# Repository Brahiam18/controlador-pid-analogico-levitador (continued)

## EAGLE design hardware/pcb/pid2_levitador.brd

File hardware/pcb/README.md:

# Placa de 2 controladores PID analógicos con etapa de potencia

Placa de **una sola cara** para fabricar en baquela (transferencia de tóner o fotosensible) con **dos controladores PID independientes**. Para el levitador de cuatro bobinas se hacen **dos tarjetas iguales** (un solo plano, impreso dos veces). Cada controlador es idéntico al circuito del informe (2 × TL074CN por PID) y **trae su propia etapa de potencia** (convertidor tensión‑corriente con TIP122, banco de sensado de 3 × 1 Ω, protección y bornes para la bobina). Los dos PID de una tarjeta comparten los rieles de ±16 V, +5 V y GND; cada uno tiene su entrada de sensor (`VSEN`), su salida de control (`VPID`), su alimentación de bobina (`VBOB`/`PGND`) y su conexión de bobina.

| Dato | Valor |
|---|---|
| Tamaño de la placa | **170.2 × 116.8 mm** (17 × 11.7 cm): cabe en una baquela de 20 × 20 cm y el PDF se imprime 1:1 en una hoja A4 o Carta |
| Capas | 1 (cobre inferior) + puentes de alambre en el lado de componentes |
| Pistas de señal / pads / taladro | 0.7 mm / 2.0 mm / 0.9 mm (los pads de potencia usan 1.0 a 1.3 mm) |
| Pistas de potencia | 2.0 mm (`ISENSE`, `COILN`, `+VBOB`, `PGND`); unos 3.9 A con +10 °C de calentamiento, conviene **cubrirlas con estaño** |
| Separación mínima entre redes | 0.45 mm (medida sobre la geometría final) |
| Puentes de alambre | 24 en total, ninguno en redes de potencia; ver [`puentes.md`](puentes.md) |

## Archivos

| Archivo | Para qué sirve |
|---|---|
| [`pid2_levitador.sch`](pid2_levitador.sch) y [`pid2_levitador.brd`](pid2_levitador.brd) | Esquemático (una hoja por PID) y placa en formato EAGLE; Fusion los abre en Electronics |
| [`cobre_espejado_1a1.pdf`](cobre_espejado_1a1.pdf) | **Hoja de cobre espejado a escala 1:1** para imprimir y quemar la placa (imprimirla dos veces: una por tarjeta) |
| [`ensamble_1a1.pdf`](ensamble_1a1.pdf) | **Hoja del lado de componentes** (3 páginas: la placa completa 1:1 y cada PID ampliado): nombre de cada pieza y de cada pin de las regletas, borneras, TIP122 y diodos, amplificadores U1 a U8 marcados sobre cada TL074 y puentes en rojo (J1 a J24) |
| [`puentes.md`](puentes.md) | Lista de los 24 puentes con red, longitud y extremos |
| [`generador/`](generador/) | Código en Python que genera todo lo anterior a partir de un módulo ruteado (`modulo_ruteado.json`) |

## Cómo usarlos

**Abrir en Fusion.** En Fusion, usar "Cargar" y elegir `pid2_levitador.sch` y `pid2_levitador.brd` juntos; con la casilla "Crear diseño de la electrónica" marcada se obtiene un solo diseño de Electronics. Las piezas están en una biblioteca propia llamada `pid4`.

**Imprimir y quemar.** Imprimir `cobre_espejado_1a1.pdf` **sin escalar** ("tamaño real", sin "ajustar a página"); la hoja mide 210 × 279 mm y entra en A4 y en Carta. La regla de 50 mm al pie de la placa sirve para comprobar la escala. La hoja ya está espejada: el tóner va contra el cobre. El punto blanco en el centro de cada pad marca dónde taladrar. Taladros: 0.9 mm en general, 1.0 mm para el TIP122, 1.1 mm para el banco de sensado y 1.3 mm para el 1N5408 y las borneras.

**Soldar.** Imprimir también `ensamble_1a1.pdf`: sirve de guía para ubicar cada pieza. Primero los puentes de alambre aislado en el lado de componentes (ver [`puentes.md`](puentes.md)), después resistencias, zócalos y diodos, y al final potenciómetros, capacitores, borneras y el TIP122. Cubrir con estaño las pistas anchas de potencia.

**Dos tarjetas.** Las dos placas son iguales. Para alimentarlas se unen por cable `+16V`, `-16V`, `GND` y `+5V` entre las regletas `J_PWR` de las dos tarjetas. El puente `JP_GND` (une la tierra de potencia con la de señal) se suelda en **una sola** de las cuatro etapas.

## Conexiones de cada PID

| Regleta | Pines | Función |
|---|---|---|
| `J_PWR` | 1 · 2 · 3 · 4 | `+16V` · `-16V` · `GND` · `+5V` (compartidos en la tarjeta: basta alimentar una sola regleta) |
| `J_IN` | 1 | `VSEN`, señal del sensor de posición |
| `J_OUT` | 1 | `VPID`, salida del controlador (1 V a 3 V); es solo punto de medida, la etapa de potencia ya lo toma internamente |
| `J_VBOB` (bornera) | `+VBOB` · `PGND` | Fuente de las bobinas: positivo y negativo. **Una fuente por PID** (o todos los pares en paralelo a la misma fuente) |
| `J_COIL` (bornera) | `BOB+` · `BOB-` | Bobina: `BOB+` va a `+VBOB` por la pista; `BOB-` va al colector del TIP122 |
| `JP_GND` | `GND` · `PGND` | Dos pads **sin pista entre ellos**: se unen con un alambre para juntar la tierra de potencia con la de señal (ver más abajo) |

`+5V` solo alimenta el divisor de `V_ref` (`R13`).

## Etapa de potencia (una por PID)

Es el circuito que armaste y simulaste en Proteus: un amplificador (U8) compara el voltaje de entrada con el voltaje sobre la resistencia de sensado y maneja la base de un TIP122, de modo que **la corriente de la bobina es proporcional a la salida del PID**. La bobina va entre `+VBOB` y el colector; el diodo 1N5408 en paralelo con la bobina absorbe el pico inductivo.

```mermaid
flowchart LR
    VPID["VPID (1 a 3 V)"] --> R17["R17 10 kΩ"] --> POT4["POT4 10 kΩ<br/>(calibración)"]
    POT4 -- cursor --> R16["R16 270 Ω"] --> U8["U8 (TL074, IC2 canal 4)<br/>entrada +"]
    U8 -- salida --> RB["RBASE 270 Ω"] --> D2["D2 1N4148<br/>(serie)"] --> Q1["Q1 TIP122"]
    Q1 -- emisor --> RS["RS: 3 × 1 Ω 5 W<br/>en paralelo = 0.33 Ω"] --> PG["PGND"]
    Q1 -- emisor / ISENSE --> R18["R18 1 kΩ"] --> U8m["U8 entrada −"]
    VB["+VBOB"] --> BOB["Bobina"] --> Q1
    D1["D1 1N5408"] -. "en paralelo con la bobina" .- BOB
```

Qué se agregó respecto a tu esquemático de Proteus, y por qué:

| Pieza | Para qué |
|---|---|
| **R17 + POT4** (divisor de calibración) | Con 3 resistencias de 1 Ω en paralelo el sensado vale **0.33 Ω**, no 1 Ω, así que la ganancia sube tres veces (`I = V/0.33 Ω`) y 3 V a la entrada pedirían 9 A. El divisor devuelve la ganancia a un valor seguro y deja ajustar la corriente sin tocar el banco de potencia |
| **D2** (1N4148 en serie con la base) | Si el amplificador satura hacia −13 V, no empuja ese voltaje inverso a la unión base‑emisor del TIP122 (máx. 5 V inverso) |
| **R18** (1 kΩ) y **C3** (10 nF, opcional) | Solo si el lazo de corriente oscila con el TL074 (más rápido que el LM741 de la simulación): soldar `C3` entre la salida de U8 y su entrada −. Sin `C3`, `R18` no tiene efecto |
| **JP_GND** | Une `PGND` con `GND` en un solo punto |

### Por qué 3 resistencias y no 10

Cada resistencia de 1 Ω conduce `I/n` y disipa `(I/n)²` vatios, y el sensado total vale `1/n` Ω. A 4.5 A (el máximo del TIP122 con margen), con `n = 3` cada una disipa 2.25 W: menos de la mitad de sus 5 W. Con `n = 10` cada una solo disiparía 0.2 W, y el banco ocupaba casi la mitad de cada módulo.

| Resistencias por PID (`n`) | `R_S` | `R17` | Cada una a 3 A | Cada una a 4.5 A |
|:-:|:-:|:-:|:-:|:-:|
| 2 (no recomendado) | 0.5 Ω | 3.3 kΩ | 2.25 W | 5 W (en el límite) |
| **3 (la huella de la placa)** | **0.33 Ω** | **10 kΩ** | **1 W** | **2.25 W** |

La huella tiene 3 posiciones. Con 2 resistencias hay que cambiar `R17` a 3.3 kΩ y no queda margen para 4.5 A; con 1 sola no sirve.

### Ganancia y calibración

`I_bobina = V_cal / R_S` con `V_cal = k · V_PID` y `R_S = 0.33 Ω` (3 resistencias), es decir:

**`I_bobina ≈ 3 · k · V_PID`** con `k = R_b / (R17 + 10 kΩ)`, donde `R_b` es la resistencia del cursor de POT4 a masa (0 a 10 kΩ). Con `R17 = 10 kΩ`, `k` va de 0 a 0.5.

| Ajuste de POT4 | `k` | Ganancia | Corriente con `V_PID` = 2 V | Con `V_PID` = 3 V |
|---|:-:|:-:|:-:|:-:|
| Mínimo (cursor a masa) | 0 | 0 | 0 A | 0 A |
| Cursor al 67 % (`R_b` = 6.7 kΩ) | 0.33 | 1 A/V (como en tu simulación) | 2.0 A | 3.0 A |
| Máximo | 0.5 | 1.5 A/V | 3.0 A | 4.5 A |

El máximo (4.5 A) queda por debajo del límite del TIP122 (5 A continuos).

**Cómo calibrar.** (1) Con POT4 al mínimo, conectar la bobina y la fuente de `VBOB` (empezar con la fuente baja). (2) Con el objeto en su posición de equilibrio, subir POT4 hasta la corriente que necesites. (3) La corriente se mide como voltaje entre `ISENSE` (emisor del TIP122) y `PGND`: **0.33 V por cada amperio**.

### Disipación y fuente

El TIP122 trabaja en modo lineal: disipa `P = (V_BOB − I·(R_bobina + 0.33 Ω)) · I`. Como la resistencia de la bobina irá cambiando, conviene consultar esta tabla (se asume `Vce` mínimo de 2 V; "no llega" significa que la fuente no alcanza para esa corriente):

| Resistencia de la bobina | 12 V: 1 A | 12 V: 2 A | 12 V: 3 A | 20 V: 1 A | 20 V: 2 A | 20 V: 3 A |
|:-:|:-:|:-:|:-:|:-:|:-:|:-:|
| 2 Ω | 10 W | 15 W | 15 W | 18 W | **31 W** | **39 W** |
| 4 Ω | 8 W | 7 W | no llega | 16 W | 23 W | 21 W |
| 6 Ω | 6 W | no llega | no llega | 14 W | 15 W | no llega |
| 8 Ω | 4 W | no llega | no llega | 12 W | 7 W | no llega |

- Con bobinas de poca resistencia y 20 V, el TIP122 disipa decenas de vatios: **disipador grande (y ventilador)** o bajar la tensión de `VBOB`.
- La aleta del TIP122 es el colector (`BOB-`): si varios transistores comparten disipador, **aislarlos** con mica o silicona.
- Una fuente de 20 V / 6 A reparte 6 A entre las cuatro etapas (1.5 A por bobina si trabajan a la vez).
- Poner un **fusible de 5 A** en cada línea de `+VBOB` (fuera de la placa) mientras se afina.
- Los offsets del TL074 (unos mV) equivalen a decenas de mA con 0.33 Ω; el lazo de posición lo compensa, pero la corriente "cero" no será exacta.
- La caída en las pistas de potencia se suma al sensado; por eso el banco y `JP_GND` están cerca.

## Reparto de las etapas en los TL074CN

El TL074CN trae 4 amplificadores en un solo DIP‑14, así que las 7 etapas del informe (U1 a U7) más el convertidor tensión‑corriente de potencia (**U8**) caben en 2 integrados por controlador. Cada integrado se llama `IC1` o `IC2` en la placa (con el prefijo del PID, por ejemplo `P1_IC1`) y en la hoja de ensamble cada canal lleva escrita su etapa (cuadro amarillo).

| Etapa | Integrado | Canal | Salida (pin) | Entrada − (pin) | Entrada + (pin) |
|---|:-:|:-:|:-:|:-:|:-:|
| U6 · buffer de `V_ref` | IC1 | 1 | 1 | 2 | 3 |
| U1 · diferenciador de error | IC1 | 2 | 7 | 6 | 5 |
| U2 · proporcional | IC1 | 3 | 8 | 9 | 10 |
| U3 · integral | IC1 | 4 | 14 | 13 | 12 |
| U4 · derivativo | IC2 | 1 | 1 | 2 | 3 |
| U5 · sumador | IC2 | 2 | 7 | 6 | 5 |
| U7 · buffer de `V_off` | IC2 | 3 | 8 | 9 | 10 |
| **U8 · convertidor V‑I de potencia** | IC2 | 4 | 14 | 13 | 12 |

Alimentación de cada TL074CN: `+16V` en el pin 4 y `-16V` en el pin 11. Los valores de resistencias y capacitores de las etapas U1 a U7 son los del informe.

## Componentes (por PID, por tarjeta y para los 4 PID)

| Componente | Por PID | Por tarjeta (2 PID) | Para 4 PID (2 tarjetas) | Notas |
|---|:-:|:-:|:-:|---|
| TL074CN (DIP14) | 2 | 4 | 8 | Usar zócalos DIP14. Pin 1 arriba a la izquierda en todos los CI |
| TIP122 (TO‑220) | 1 | 2 | 4 | Con disipador; el pad cuadrado es la base (B), el del centro el colector (C) y el otro el emisor (E) |
| 1N5408 | 1 | 2 | 4 | `D1`, protección de la bobina. La raya marca el cátodo (pad hacia `+VBOB`) |
| 1N4148 | 1 | 2 | 4 | `D2`, en serie con la base. La raya marca el cátodo (pad hacia la base) |
| 1 Ω / 5 W axial | 3 | 6 | 12 | Banco `RS`; ver arriba por qué 3 |
| 10 kΩ | 10 | 20 | 40 | R1, R2, R3, R4, R5, R7, R8, R9, R_offset y R17 |
| 1 kΩ | 3 | 6 | 12 | R6, R10 y R18 |
| 270 Ω | 2 | 4 | 8 | R16 y RBASE |
| 1 MΩ | 1 | 2 | 4 | R11 |
| 160 kΩ | 2 | 4 | 8 | R12, R15 |
| 240 kΩ | 1 | 2 | 4 | R13 |
| 96 kΩ | 1 | 2 | 4 | R14 (valor calculado; no es de serie, ver más abajo) |
| 4.4 kΩ | 1 | 2 | 4 | R_bias (valor de tu montaje; no es de serie, ver más abajo) |
| Potenciómetro 22 kΩ | 2 | 4 | 8 | Pot1 (Kp) y Pot3 (Kd) |
| Potenciómetro 220 kΩ | 1 | 2 | 4 | Pot2 (Ki) |
| Potenciómetro 10 kΩ | 1 | 2 | 4 | Pot4 (corriente de la bobina) |
| Capacitor 1 µF | 2 | 4 | 8 | C1 (integrador) y C2 (derivador) |
| Capacitor 10 nF | 0 (opcional 1) | 0 (opcional 2) | 0 (opcional 4) | C3, solo si el lazo de corriente oscila |
| Borneras de tornillo de 2 vías, paso 5.08 | 2 | 4 | 8 | `J_VBOB` y `J_COIL` (corriente de varios amperios) |
| Regletas de pines | 8 pines | 16 pines | 32 pines | 1 × 4 (`J_PWR`), 2 × 1 (`J_IN`, `J_OUT`) y 1 × 2 (`JP_GND`) |

Resistencias axiales de 1/4 W a 7.62 mm, capacitores a 5.08 mm y potenciómetros de 3 pines a 5.08 mm (pin 1 = extremo, pin 2 = cursor, pin 3 = otro extremo). Las resistencias de 5 W miden unos 22 × 9.5 mm y se montan acostadas con 25.4 mm entre pads, en una fila de tres.

## Cosas a tener en cuenta

- **Capacitores sin polaridad.** `C1` y `C2` trabajan con señales de ambos signos, por lo que conviene usar poliéster (MKT) o cerámicos de 1 µF. Con un electrolítico, la polaridad queda invertida en una parte del ciclo.
- **`R_bias` y `R14` no son valores comerciales.** Para `R_bias` sirven 4.7 kΩ o 4.3 kΩ (la corriente de polarización es muy pequeña). Para `R14`, tomar 100 kΩ o 91 kΩ más 4.7 kΩ en serie y ajustar mirando `V_off`: en la protoboard se midieron −10.21 V frente a −10.1 V calculados. El informe sigue con `R14` como "falta medir" y con la errata 5 de `R_bias` sin resolver.
- **TL074CN en lugar de LM741.** La placa está hecha para el TL074CN. El informe, la lista de materiales general y las mediciones de la Tabla I todavía nombran al LM741; con TL074CN (entradas JFET, salida de unos ±13 V con ±16 V) los offsets y los valores prácticos pueden cambiar un poco.
- **Diferenciador (U1).** La placa sigue el esquemático de Proteus y las mediciones del montaje: `R1` recibe `V_ref` (entrada inversora) y `R3` recibe `V_sensor` (entrada no inversora), así que `V_e = V_sensor − V_ref`. La tabla de nomenclatura del informe dice lo contrario para `R1` y `R3`; conviene corregirla.
- **`V_ref` fijo.** `R12`/`R13` dan 2 V de referencia. Con un sensor Hall lineal (por ejemplo SS495A) el voltaje en el punto de equilibrio será cercano a 2.5 V más el aporte del imán, así que probablemente haga falta ajustar `V_ref` (por ejemplo con un trimmer en lugar de `R12`).
- **Puentes.** Son 24 en total (ninguno en redes de potencia); los más largos miden hasta unos 71 mm de alambre y varios pasan sobre otros componentes, por eso deben ser de alambre aislado. En el archivo EAGLE los puentes están dibujados en la capa Top.
- **Sin decoupling.** El diseño del informe no incluye capacitores de desacople; si hay ruido, se pueden soldar 100 nF entre cada alimentación del TL074CN (pines 4 y 11) y masa por el lado de soldadura.
- **Polaridad del control.** Si al subir `V_PID` la bobina atrae más o menos depende del sensor y del montaje; esta placa solo entrega corriente proporcional a `V_PID`.

## Qué se verificó y qué no

Verificado con scripts incluidos en [`generador/`](generador/) (`verify.py` y `xmlcheck.py`):
- Las 62 redes de la placa están completas (ningún pad queda sin conectar a su red) y no hay cortos entre redes.
- La separación mínima entre cobre de redes distintas es de 0.45 mm, también entre las pistas anchas de 2.0 mm.
- Los puentes no tocan pads ajenos ni se cruzan entre sí, y ninguna red de potencia usa puentes.
- El esquemático y la placa tienen las mismas piezas y las mismas conexiones.

**No** verificado: la placa no se ha fabricado ni probado, y el comportamiento de la etapa de potencia con el TL074CN (estabilidad del lazo de corriente, calentamiento) no se simuló: sale de tu esquemático de Proteus y de cálculos a mano. Las versiones anteriores de la placa se importaron en Fusion sin errores; esta versión usa el mismo exportador pero con símbolos nuevos (transistor, diodos, banco de sensado) y aún no se ha reabierto en Fusion. Los archivos `.sch` y `.brd` se escribieron a mano en el formato XML de EAGLE; si Fusion muestra algún aviso al importarlos, conviene revisarlo antes de quemar. Se recomienda probar un solo PID (con la bobina real a baja tensión y un fusible) antes de armar el resto.

## Regenerar

```bash
cd generador
pip install numpy matplotlib shapely
python3 build.py modulo_ruteado.json salida
```

Genera en `salida/` los archivos `.sch`, `.brd`, los dos PDF y la lista de puentes. Para buscar otra colocación y ruteo del módulo (otro tamaño o semilla): `python3 buscar_modulo.py 30 42 1,2,3 prueba` y luego `python3 a_json.py best_prueba.pkl modulo_ruteado.json`. El número de PID por tarjeta está en `assemble.py` (`NMOD`).

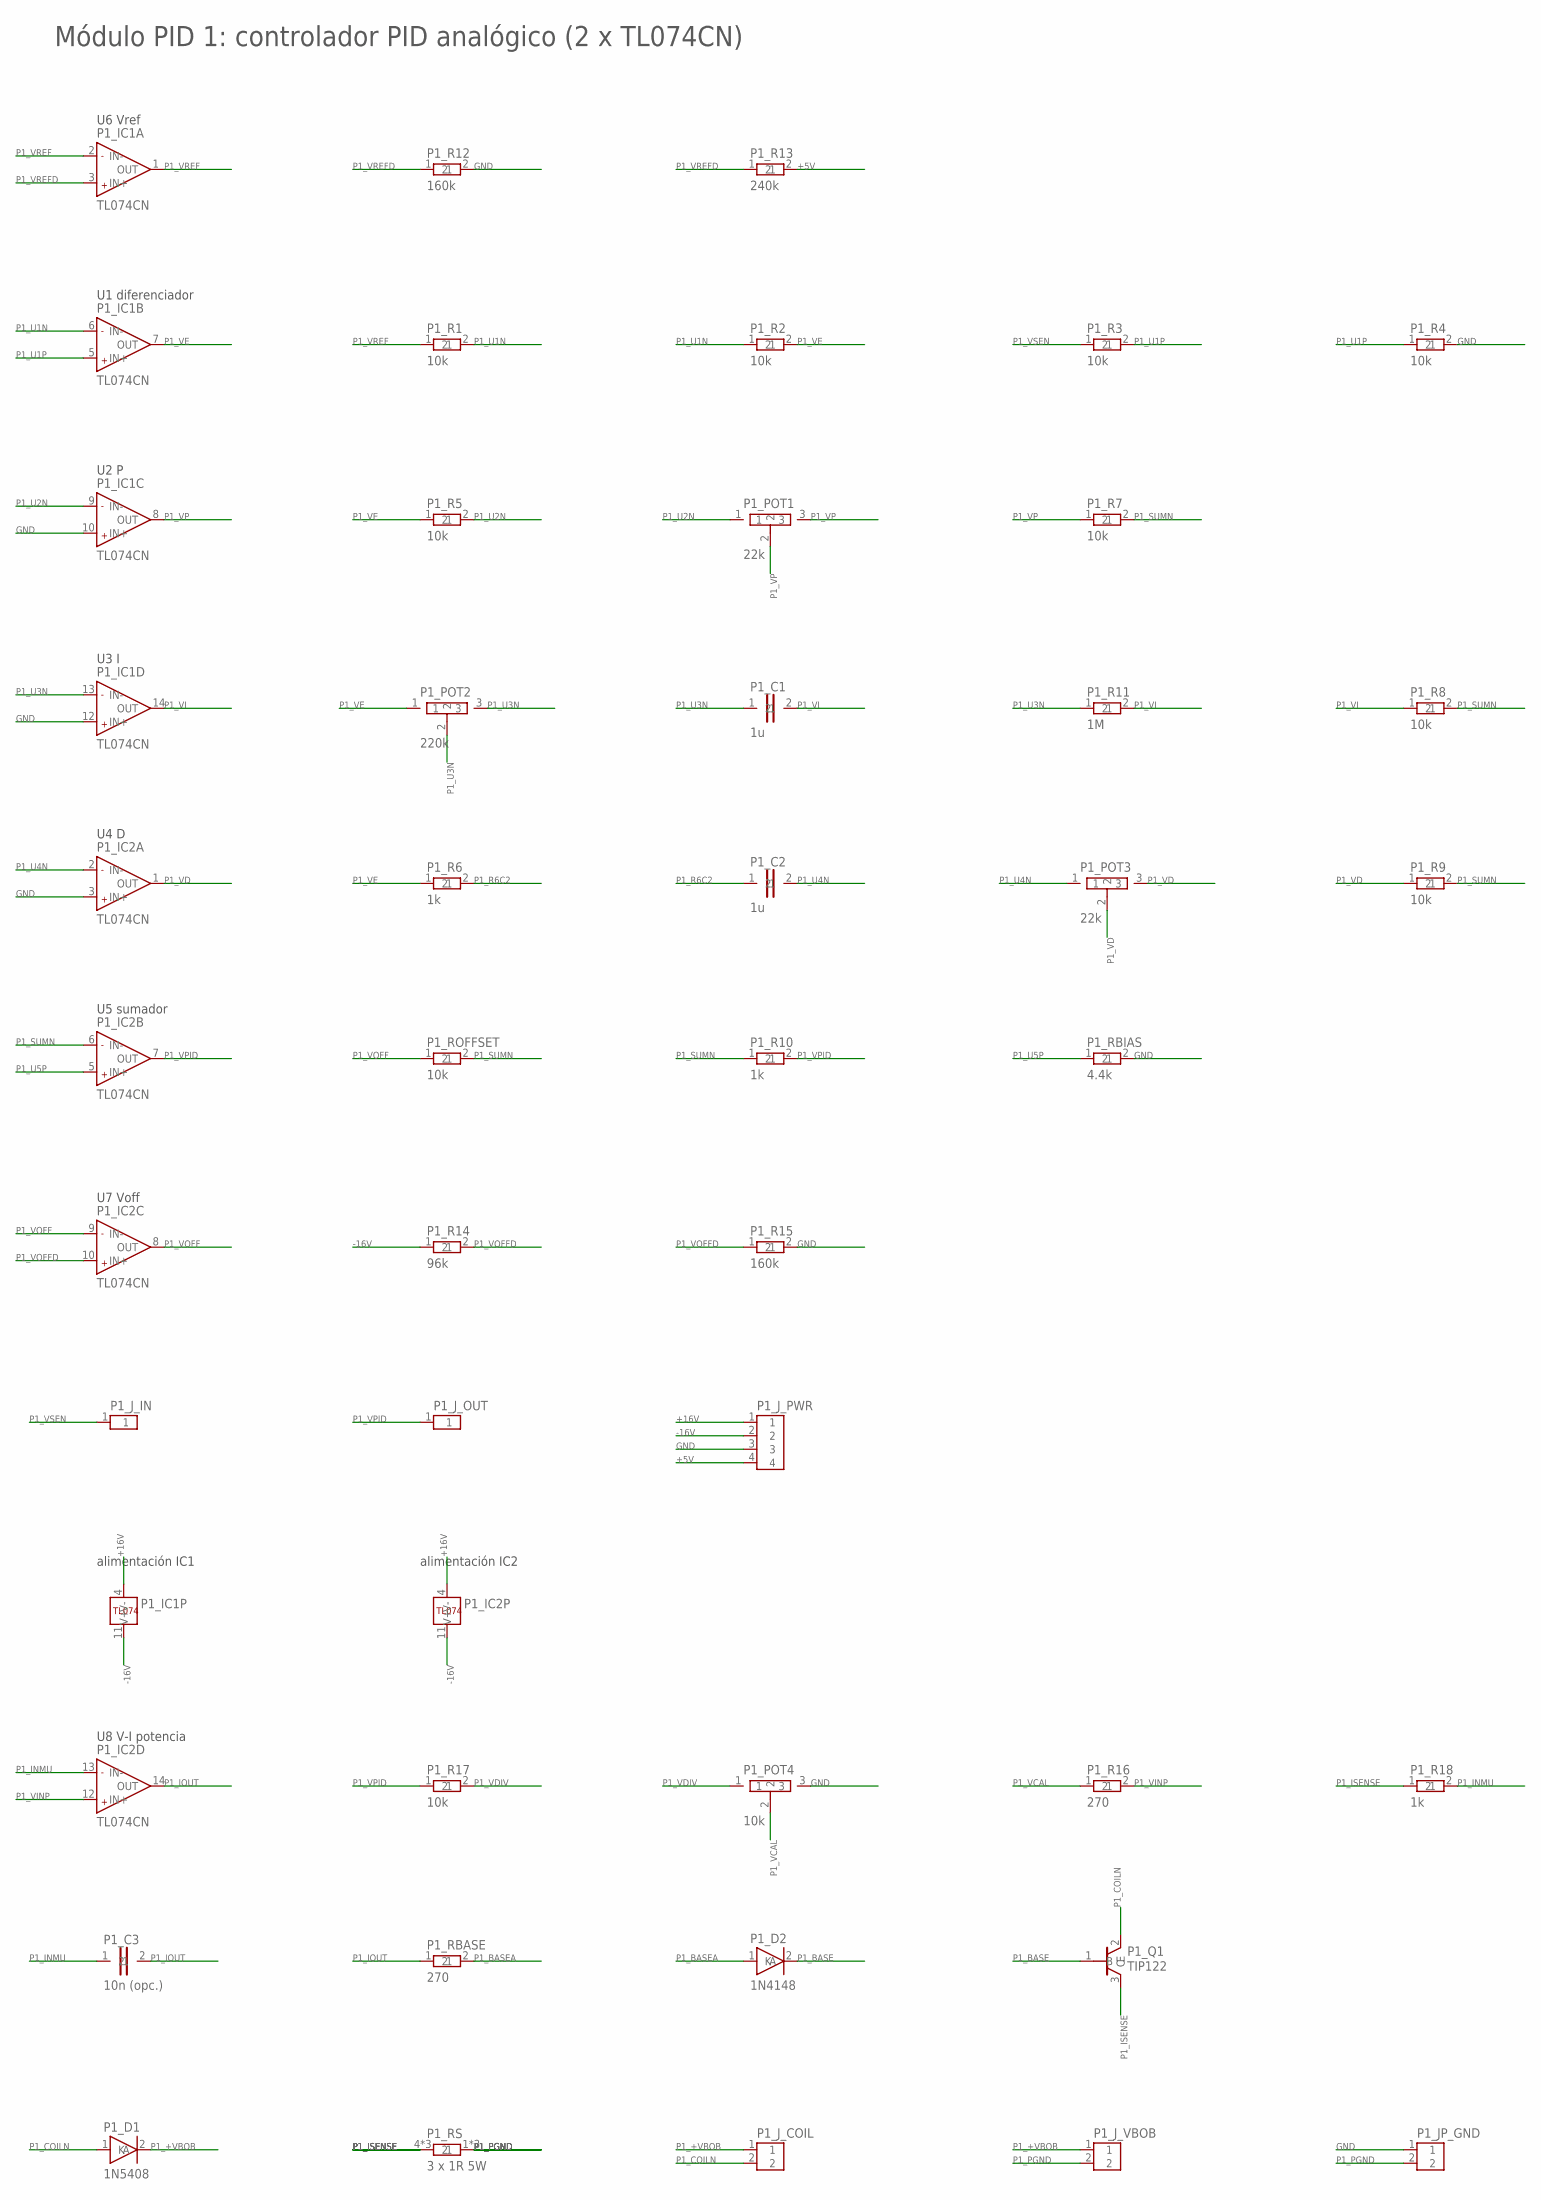
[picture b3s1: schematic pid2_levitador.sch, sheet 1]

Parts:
P1_C1, P1_C2: 1u; CAP
P1_C3: 10n (opc.); CAP
P1_D1: 1N5408; DIODE
P1_D2: 1N4148; DIODE_S
P1_IC1, P1_IC2: TL074CN; DIL14
P1_JP_GND: GND-PGND; HDR2
P1_J_COIL: BOBINA; TERM2
P1_J_IN: VSENSOR; HDR1
P1_J_OUT: VPID; HDR1
P1_J_PWR: PWR; HDR4
P1_J_VBOB: VBOB; TERM2
P1_POT1, P1_POT3: 22k; POT
P1_POT2: 220k; POT
P1_POT4: 10k; POT
P1_Q1: TIP122; TO220
P1_R1, P1_R2, P1_R3, P1_R4, P1_R5, P1_R7, P1_R8, P1_R9, P1_R17, P1_ROFFSET: 10k; RES
P1_R6, P1_R10, P1_R18: 1k; RES
P1_R11: 1M; RES
P1_R12, P1_R15: 160k; RES
P1_R13: 240k; RES
P1_R14: 96k; RES
P1_R16, P1_RBASE: 270; RES
P1_RBIAS: 4.4k; RES
P1_RS: 3 x 1R 5W; RSBANK

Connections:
+5V: P1_J_PWR.4, P1_R13.2; also elsewhere on the board
+16V: P1_IC1.4 (V+), P1_IC2.4 (V+), P1_J_PWR.1; also elsewhere on the board
-16V: P1_IC1.11 (V-), P1_IC2.11 (V-), P1_J_PWR.2, P1_R14.1; also elsewhere on the board
GND: P1_IC1.10 (IN+), P1_IC1.12 (IN+), P1_IC2.3 (IN+), P1_JP_GND.1, P1_J_PWR.3, P1_POT4.3, P1_R4.2, P1_R12.2, P1_R15.2, P1_RBIAS.2; also elsewhere on the board
P1_+VBOB: P1_D1.2 (K), P1_J_COIL.1, P1_J_VBOB.1
P1_BASE: P1_D2.2 (K), P1_Q1.1 (B)
P1_BASEA: P1_D2.1 (A), P1_RBASE.2
P1_COILN: P1_D1.1 (A), P1_J_COIL.2, P1_Q1.2 (C)
P1_INMU: P1_C3.1, P1_IC2.13 (IN-), P1_R18.2
P1_IOUT: P1_C3.2, P1_IC2.14 (OUT), P1_RBASE.1
P1_ISENSE: P1_Q1.3 (E), P1_R18.1, P1_RS.4 (1), P1_RS.5 (1), P1_RS.6 (1)
P1_PGND: P1_JP_GND.2, P1_J_VBOB.2, P1_RS.1 (2), P1_RS.2, P1_RS.3 (2)
P1_R6C2: P1_C2.1, P1_R6.2
P1_SUMN: P1_IC2.6 (IN-), P1_R7.2, P1_R8.2, P1_R9.2, P1_R10.1, P1_ROFFSET.2
P1_U1N: P1_IC1.6 (IN-), P1_R1.2, P1_R2.1
P1_U1P: P1_IC1.5 (IN+), P1_R3.2, P1_R4.1
P1_U2N: P1_IC1.9 (IN-), P1_POT1.1, P1_R5.2
P1_U3N: P1_C1.1, P1_IC1.13 (IN-), P1_POT2.2, P1_POT2.3, P1_R11.1
P1_U4N: P1_C2.2, P1_IC2.2 (IN-), P1_POT3.1
P1_U5P: P1_IC2.5 (IN+), P1_RBIAS.1
P1_VCAL: P1_POT4.2, P1_R16.1
P1_VD: P1_IC2.1 (OUT), P1_POT3.2, P1_POT3.3, P1_R9.1
P1_VDIV: P1_POT4.1, P1_R17.2
P1_VE: P1_IC1.7 (OUT), P1_POT2.1, P1_R2.2, P1_R5.1, P1_R6.1
P1_VI: P1_C1.2, P1_IC1.14 (OUT), P1_R8.1, P1_R11.2
P1_VINP: P1_IC2.12 (IN+), P1_R16.2
P1_VOFF: P1_IC2.8 (OUT), P1_IC2.9 (IN-), P1_ROFFSET.1
P1_VOFFD: P1_IC2.10 (IN+), P1_R14.2, P1_R15.1
P1_VP: P1_IC1.8 (OUT), P1_POT1.2, P1_POT1.3, P1_R7.1
P1_VPID: P1_IC2.7 (OUT), P1_J_OUT.1, P1_R10.2, P1_R17.1
P1_VREF: P1_IC1.1 (OUT), P1_IC1.2 (IN-), P1_R1.1
P1_VREFD: P1_IC1.3 (IN+), P1_R12.1, P1_R13.1
P1_VSEN: P1_J_IN.1, P1_R3.1

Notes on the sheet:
U6 Vref
U1 diferenciador
U2 P
U3 I
U4 D
U5 sumador
U7 Voff
alimentación IC1
alimentación IC2
U8 V-I potencia
Módulo PID 1: controlador PID analógico (2 x TL074CN)

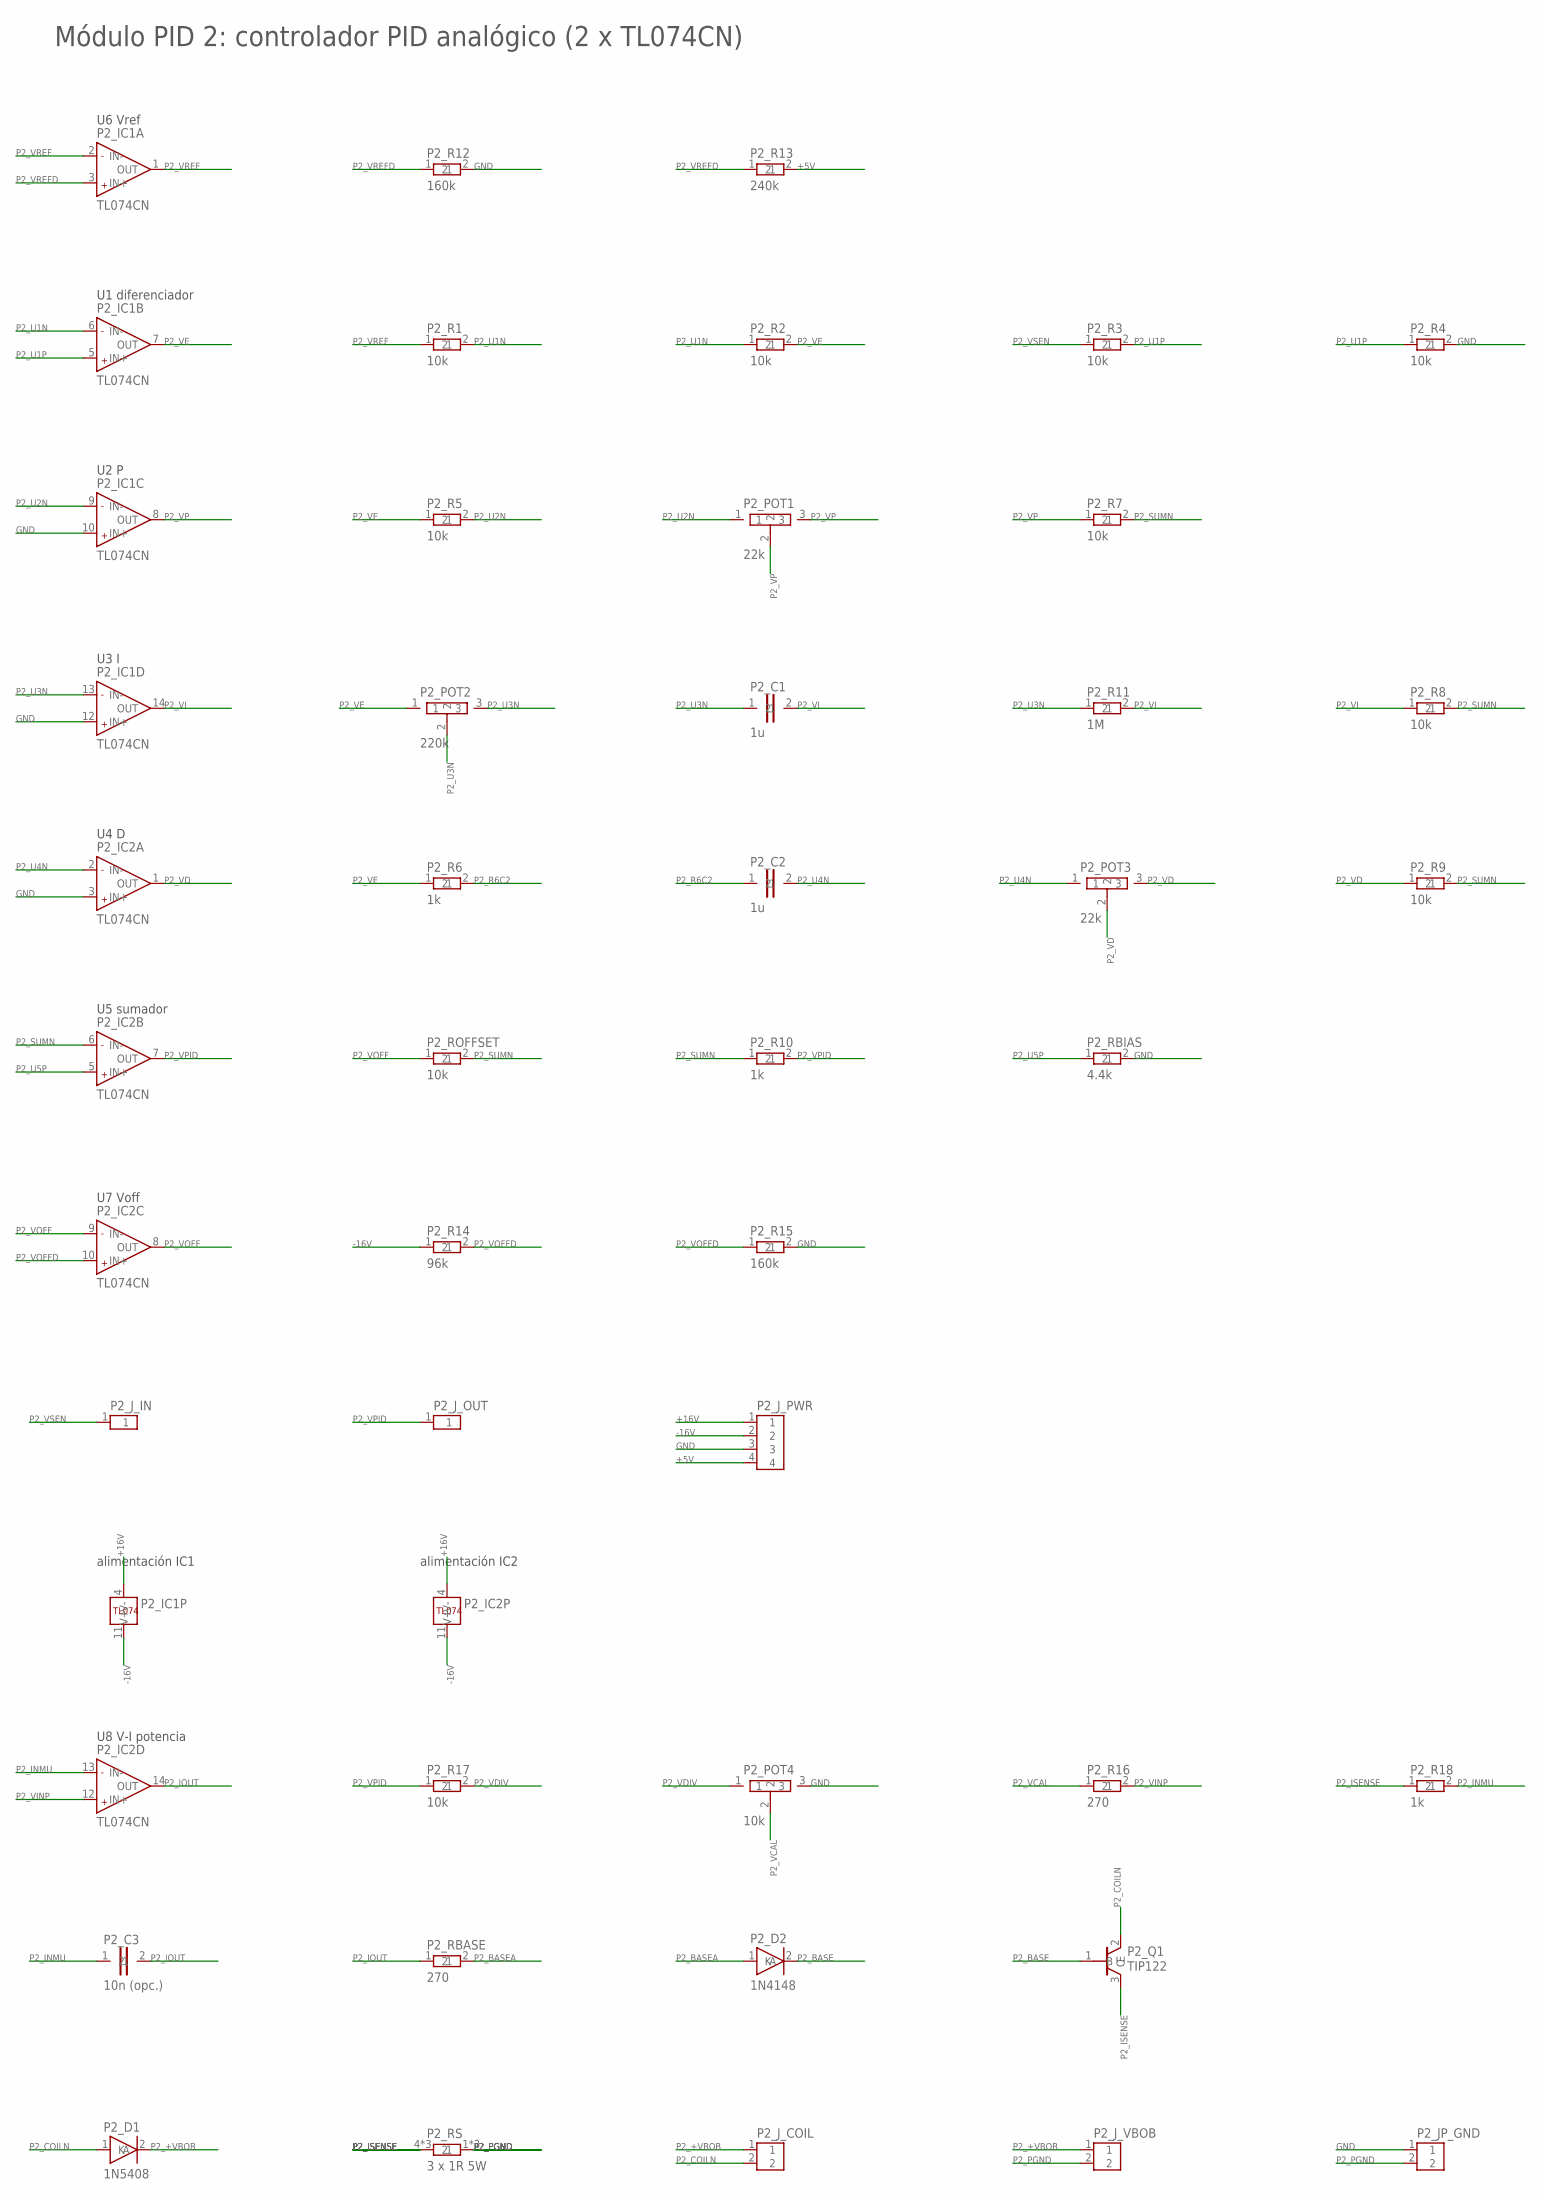
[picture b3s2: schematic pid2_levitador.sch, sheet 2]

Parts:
P2_C1, P2_C2: 1u; CAP
P2_C3: 10n (opc.); CAP
P2_D1: 1N5408; DIODE
P2_D2: 1N4148; DIODE_S
P2_IC1, P2_IC2: TL074CN; DIL14
P2_JP_GND: GND-PGND; HDR2
P2_J_COIL: BOBINA; TERM2
P2_J_IN: VSENSOR; HDR1
P2_J_OUT: VPID; HDR1
P2_J_PWR: PWR; HDR4
P2_J_VBOB: VBOB; TERM2
P2_POT1, P2_POT3: 22k; POT
P2_POT2: 220k; POT
P2_POT4: 10k; POT
P2_Q1: TIP122; TO220
P2_R1, P2_R2, P2_R3, P2_R4, P2_R5, P2_R7, P2_R8, P2_R9, P2_R17, P2_ROFFSET: 10k; RES
P2_R6, P2_R10, P2_R18: 1k; RES
P2_R11: 1M; RES
P2_R12, P2_R15: 160k; RES
P2_R13: 240k; RES
P2_R14: 96k; RES
P2_R16, P2_RBASE: 270; RES
P2_RBIAS: 4.4k; RES
P2_RS: 3 x 1R 5W; RSBANK

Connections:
+5V: P2_J_PWR.4, P2_R13.2; also elsewhere on the board
+16V: P2_IC1.4 (V+), P2_IC2.4 (V+), P2_J_PWR.1; also elsewhere on the board
-16V: P2_IC1.11 (V-), P2_IC2.11 (V-), P2_J_PWR.2, P2_R14.1; also elsewhere on the board
GND: P2_IC1.10 (IN+), P2_IC1.12 (IN+), P2_IC2.3 (IN+), P2_JP_GND.1, P2_J_PWR.3, P2_POT4.3, P2_R4.2, P2_R12.2, P2_R15.2, P2_RBIAS.2; also elsewhere on the board
P2_+VBOB: P2_D1.2 (K), P2_J_COIL.1, P2_J_VBOB.1
P2_BASE: P2_D2.2 (K), P2_Q1.1 (B)
P2_BASEA: P2_D2.1 (A), P2_RBASE.2
P2_COILN: P2_D1.1 (A), P2_J_COIL.2, P2_Q1.2 (C)
P2_INMU: P2_C3.1, P2_IC2.13 (IN-), P2_R18.2
P2_IOUT: P2_C3.2, P2_IC2.14 (OUT), P2_RBASE.1
P2_ISENSE: P2_Q1.3 (E), P2_R18.1, P2_RS.4 (1), P2_RS.5 (1), P2_RS.6 (1)
P2_PGND: P2_JP_GND.2, P2_J_VBOB.2, P2_RS.1 (2), P2_RS.2, P2_RS.3 (2)
P2_R6C2: P2_C2.1, P2_R6.2
P2_SUMN: P2_IC2.6 (IN-), P2_R7.2, P2_R8.2, P2_R9.2, P2_R10.1, P2_ROFFSET.2
P2_U1N: P2_IC1.6 (IN-), P2_R1.2, P2_R2.1
P2_U1P: P2_IC1.5 (IN+), P2_R3.2, P2_R4.1
P2_U2N: P2_IC1.9 (IN-), P2_POT1.1, P2_R5.2
P2_U3N: P2_C1.1, P2_IC1.13 (IN-), P2_POT2.2, P2_POT2.3, P2_R11.1
P2_U4N: P2_C2.2, P2_IC2.2 (IN-), P2_POT3.1
P2_U5P: P2_IC2.5 (IN+), P2_RBIAS.1
P2_VCAL: P2_POT4.2, P2_R16.1
P2_VD: P2_IC2.1 (OUT), P2_POT3.2, P2_POT3.3, P2_R9.1
P2_VDIV: P2_POT4.1, P2_R17.2
P2_VE: P2_IC1.7 (OUT), P2_POT2.1, P2_R2.2, P2_R5.1, P2_R6.1
P2_VI: P2_C1.2, P2_IC1.14 (OUT), P2_R8.1, P2_R11.2
P2_VINP: P2_IC2.12 (IN+), P2_R16.2
P2_VOFF: P2_IC2.8 (OUT), P2_IC2.9 (IN-), P2_ROFFSET.1
P2_VOFFD: P2_IC2.10 (IN+), P2_R14.2, P2_R15.1
P2_VP: P2_IC1.8 (OUT), P2_POT1.2, P2_POT1.3, P2_R7.1
P2_VPID: P2_IC2.7 (OUT), P2_J_OUT.1, P2_R10.2, P2_R17.1
P2_VREF: P2_IC1.1 (OUT), P2_IC1.2 (IN-), P2_R1.1
P2_VREFD: P2_IC1.3 (IN+), P2_R12.1, P2_R13.1
P2_VSEN: P2_J_IN.1, P2_R3.1

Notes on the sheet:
U6 Vref
U1 diferenciador
U2 P
U3 I
U4 D
U5 sumador
U7 Voff
alimentación IC1
alimentación IC2
U8 V-I potencia
Módulo PID 2: controlador PID analógico (2 x TL074CN)

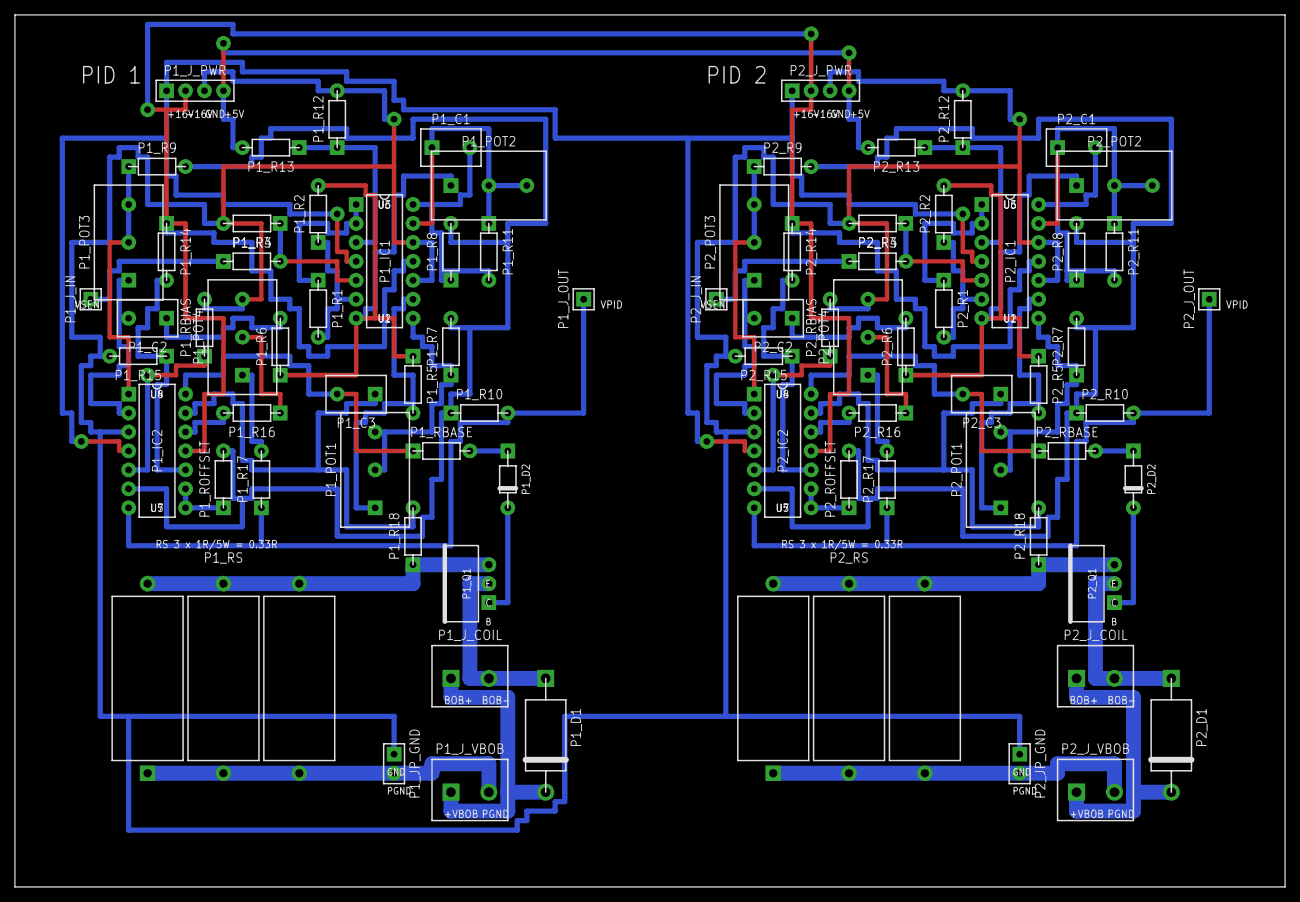
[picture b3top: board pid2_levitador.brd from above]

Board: 2 copper layers, 170.2 x 116.8 mm, 80 parts (0 on the bottom side), 62 nets.
